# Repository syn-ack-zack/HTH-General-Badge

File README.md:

## Hackers Teaching Hackers General Badge

##### Art Design and PCB Implementation: [mcm3nac3](https://twitter.com/mcm3nac3)

The general attendee badge for HTH 2019 was a PCB with the necessary circuit to allow for a USB or battery powered [Shitty Add-On (SAO)](https://hackaday.io/project/52950-shitty-add-ons) Totem badge supporting up to 4 diferent add-ons. The necessary components to enable your badge to be powered can be found in the bill of materials.   

Included in this repository are the necessary KiCad files for modifying this design and creating the necessary outputs for manufacturing. The gerber files for fabrication have been included as well for your convenience.

The bill of materials can be observed in the file `hth-gen-bom.csv`. A digikey cart can also be [viewed here](https://www.digikey.com/short/p9q0p7) which contains the necessary components to 'electrify' your badge.

*Note: An error exists in the traces around the switch for the badge. You must bridge the middle pins of the slide switch as seen in the bottom-right of the picture below.*

### Schematic

### Footprints

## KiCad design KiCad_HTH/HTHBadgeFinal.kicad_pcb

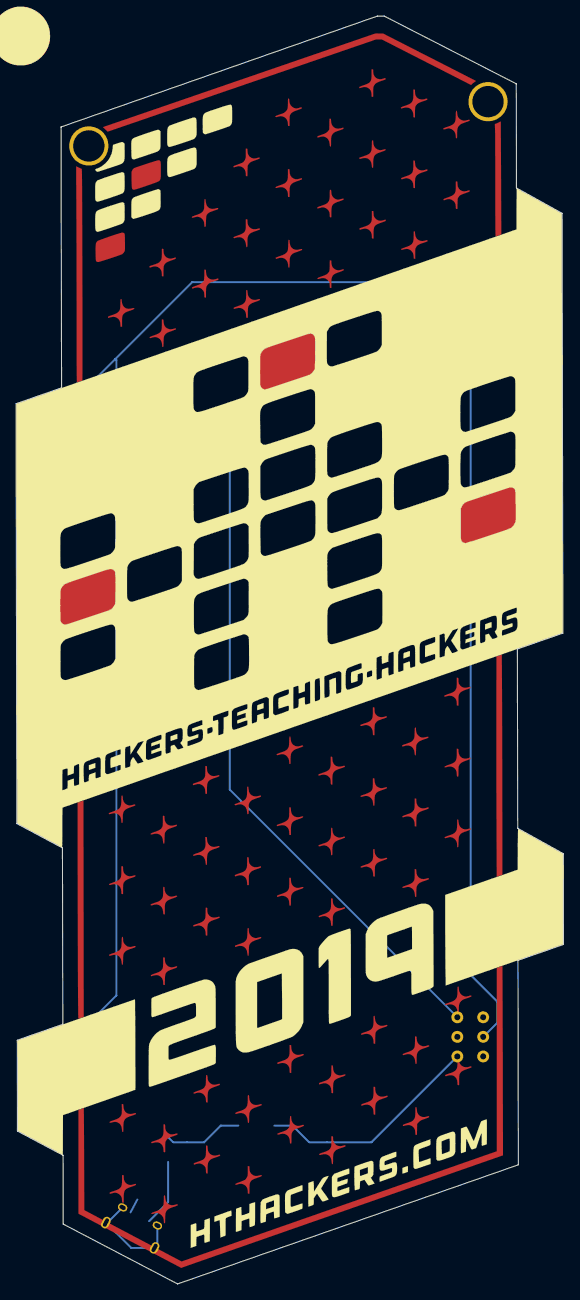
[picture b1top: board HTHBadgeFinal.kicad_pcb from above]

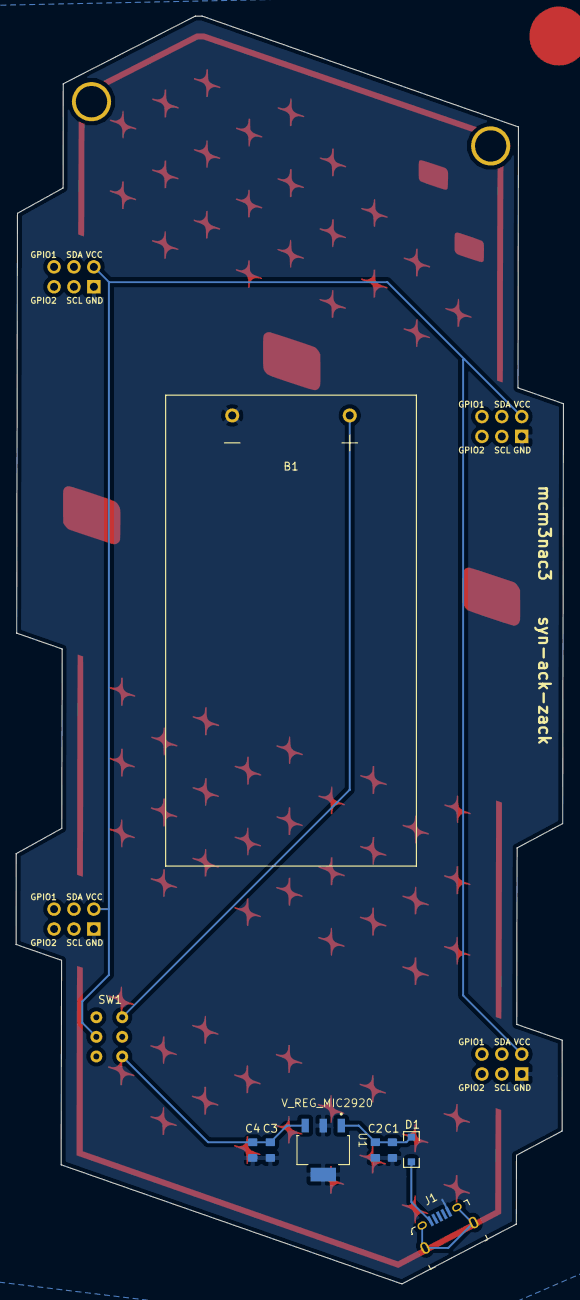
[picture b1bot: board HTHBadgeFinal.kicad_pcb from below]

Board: 2 copper layers, 69.8 x 161.8 mm, 13 parts (9 on the bottom side), 6 nets.

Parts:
B1: 2xAA; Keystone 2462 2xAA
C1, C4: CP1; CL10A105KO8NNNC
C2, C3: C; CL10A105KO8NNNC
D1: D_Schottky; B140HW-7
J1: 10118194-0001LF; USB_Micro_B_Female_10118194-0001LF
SW1: DPDT; JS202011AQN
U1: V_REG_MIC2920; SOT230P700X180-4N
X1, X2, X3, X4: Badgelife_sao_connector_v169bis; Badgelife-SAOv169-BADGE-2x3

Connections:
GND: B1.1, C1.2, C2.2, C3.2, C4.2, J1.5, U1.2, U1.4, X1.2, X2.2, X3.2, X4.2
unnamed: B1.2, SW1.4
unnamed: C1.1, C2.1, D1.1, U1.1
unnamed: C3.1, C4.1, SW1.6, U1.3
unnamed: D1.2, J1.1
unnamed: SW1.2, X1.1, X2.1, X3.1, X4.1
